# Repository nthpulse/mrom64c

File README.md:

# mrom64c
char and kernal rom replacement for the c64 250469 board

part of the MROM64 project: https://nthpulse.net/projects/mrom64/

details & instruction for this circuit board:
https://nthpulse.net/projects/mrom64/boards/mrom64c/

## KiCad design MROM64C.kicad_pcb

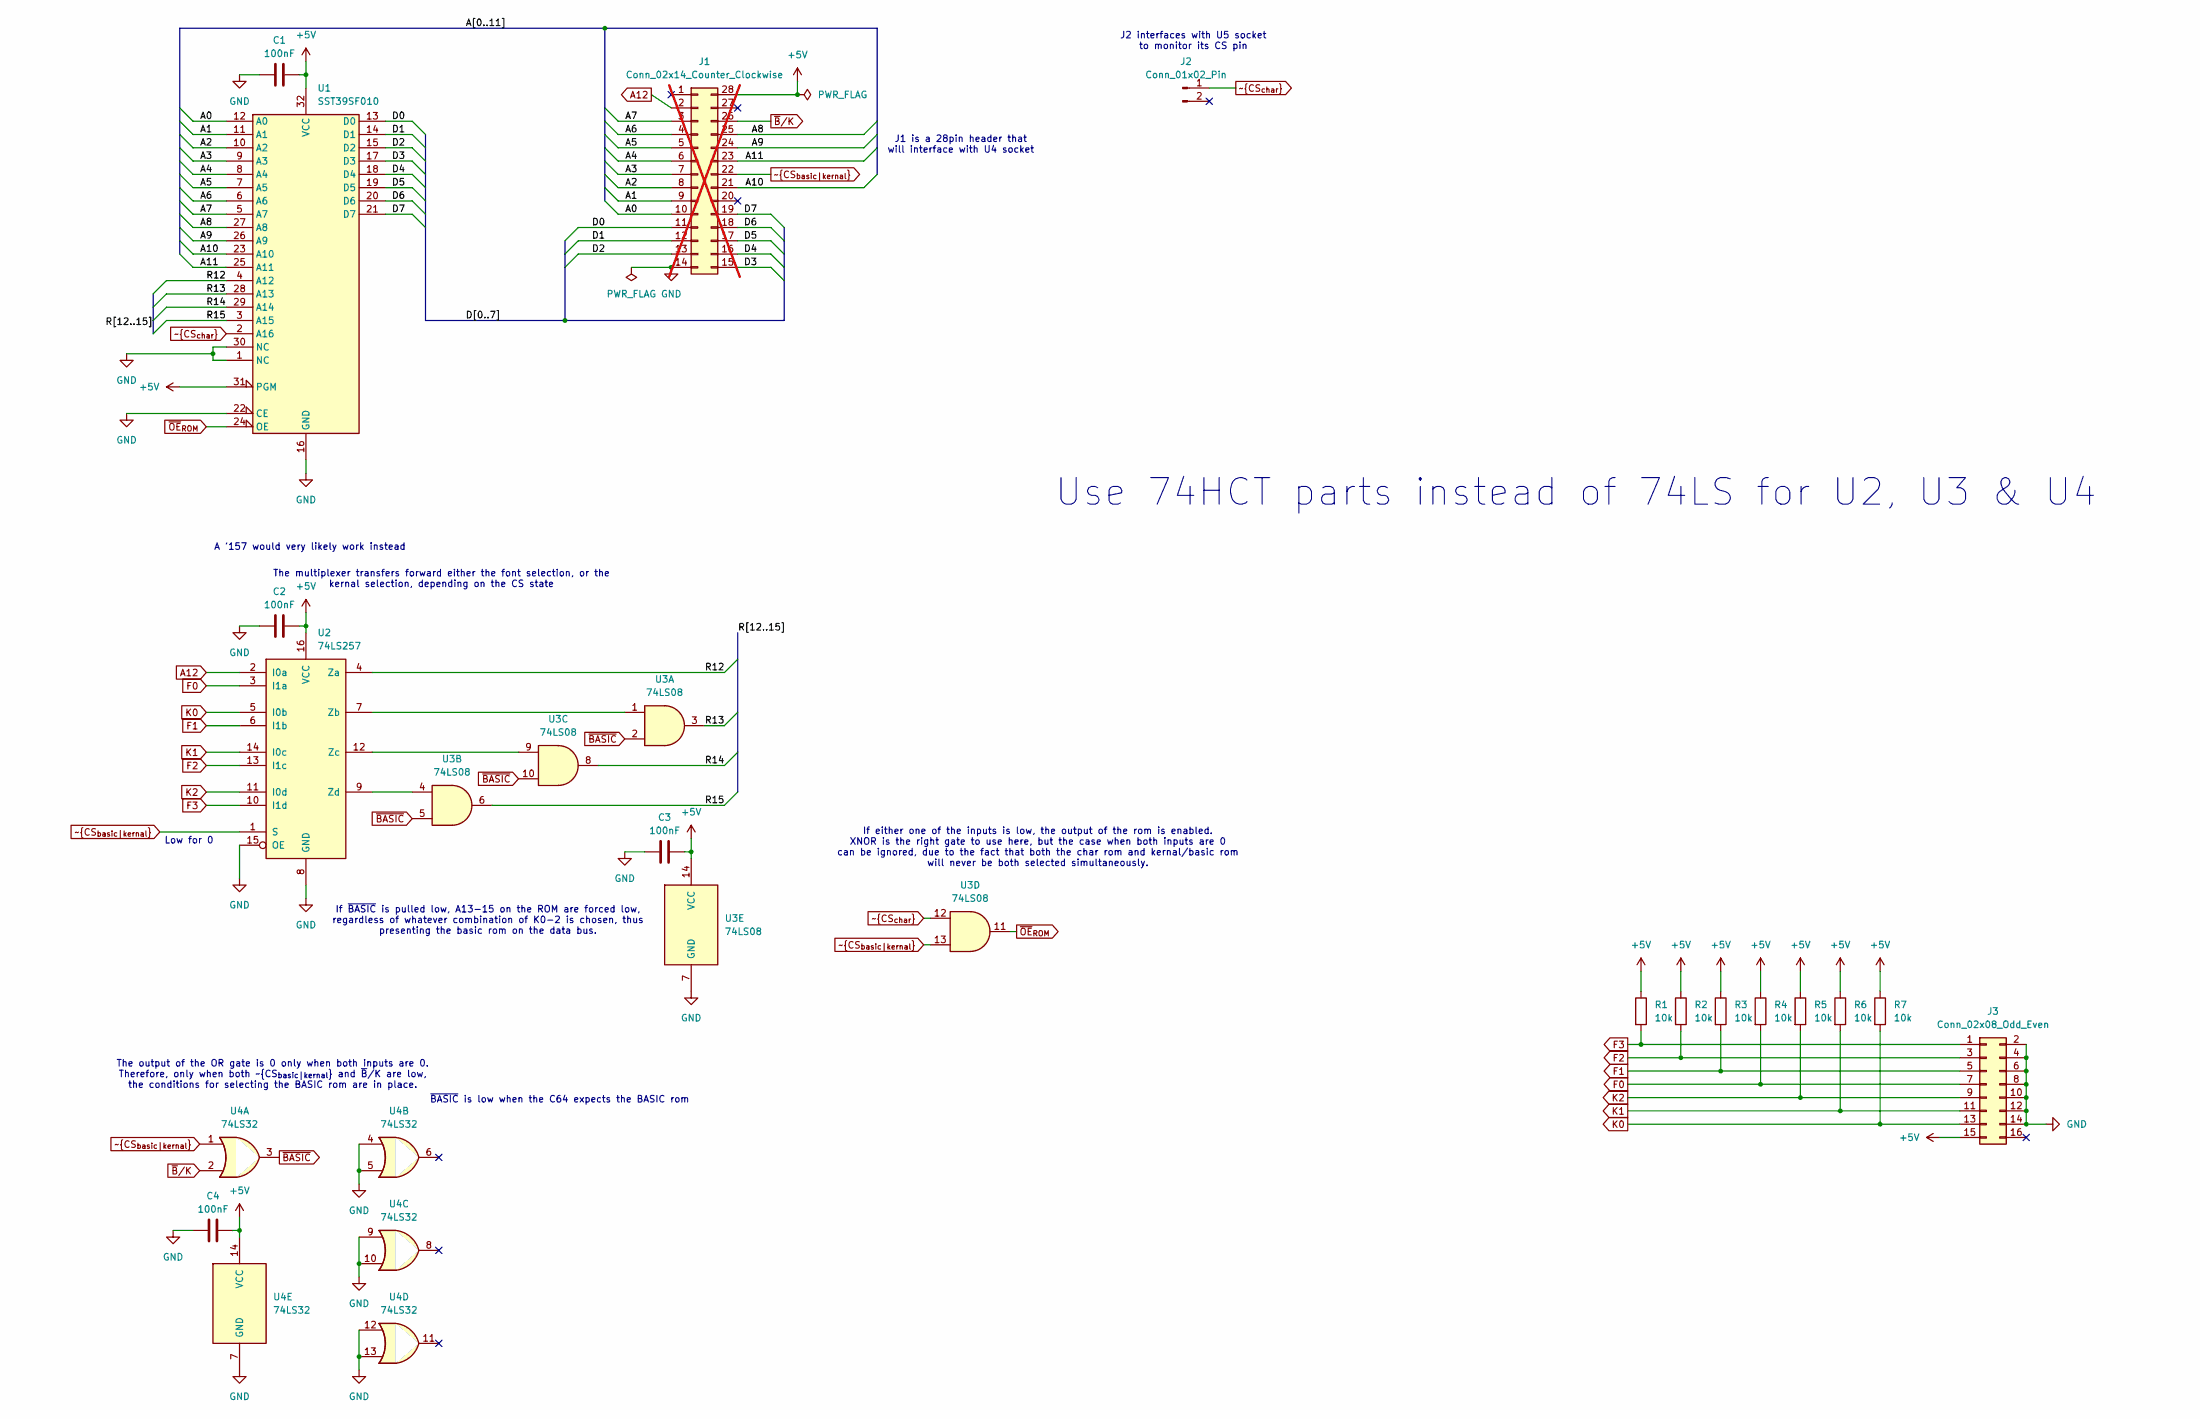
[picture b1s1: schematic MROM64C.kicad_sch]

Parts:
C1, C2, C3, C4: 100nF; C_0805_2012Metric_Pad1.18x1.45mm_HandSolder
J1: Conn_02x14_Counter_Clockwise; DIP-28_W15.24mm; not fitted
J2: Conn_01x02_Pin; PinHeader_1x02_P2.54mm_Vertical
J3: Conn_02x08_Odd_Even; PinHeader_2x08_P2.54mm_Vertical
R1, R2, R3, R4, R5, R6, R7: 10k; R_0805_2012Metric_Pad1.15x1.40mm_HandSolder
U1: SST39SF010; DIP-32_W15.24mm_Socket
U2: 74LS257; SOIC-16_3.9x9.9mm_P1.27mm
U3: 74LS08; SOIC-14_3.9x8.7mm_P1.27mm
U4: 74LS32; SOIC-14_3.9x8.7mm_P1.27mm

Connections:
+5V: C1.2, C2.2, C3.2, C4.2, J1.28, J3.15, R1.1, R2.1, R3.1, R4.1, R5.1, R6.1, R7.1, U1.31 (PGM), U1.32 (VCC), U2.16 (VCC), U3.14 (VCC), U4.14 (VCC)
/A0: J1.10, U1.12 (A0)
/A1: J1.9, U1.11 (A1)
/A2: J1.8, U1.10 (A2)
/A3: J1.7, U1.9 (A3)
/A4: J1.6, U1.8 (A4)
/A5: J1.5, U1.7 (A5)
/A6: J1.4, U1.6 (A6)
/A7: J1.3, U1.5 (A7)
/A8: J1.25, U1.27 (A8)
/A9: J1.24, U1.26 (A9)
/A10: J1.21, U1.23 (A10)
/A11: J1.23, U1.25 (A11)
/D0: J1.11, U1.13 (D0)
/D1: J1.12, U1.14 (D1)
/D2: J1.13, U1.15 (D2)
/D3: J1.15, U1.17 (D3)
/D4: J1.16, U1.18 (D4)
/D5: J1.17, U1.19 (D5)
/D6: J1.18, U1.20 (D6)
/D7: J1.19, U1.21 (D7)
/R12: U1.4 (A12), U2.4 (Za)
/R13: U1.28 (A13), U3.3
/R14: U1.29 (A14), U3.8
/R15: U1.3 (A15), U3.6
A12: J1.2, U2.2 (I0a)
F0: J3.7, R4.2, U2.3 (I1a)
F1: J3.5, R3.2, U2.6 (I1b)
F2: J3.3, R2.2, U2.13 (I1c)
F3: J3.1, R1.2, U2.10 (I1d)
GND: C1.1, C2.1, C3.1, C4.1, J1.14, J3.2, J3.4, J3.6, J3.8, J3.10, J3.12, J3.14, U1.1 (NC), U1.16 (GND), U1.22 (CE), U1.30 (NC), U2.8 (GND), U2.15 (OE), U3.7 (GND), U4.4, U4.5, U4.7 (GND), U4.9, U4.10, U4.12, U4.13
K0: J3.13, R7.2, U2.5 (I0b)
K1: J3.11, R6.2, U2.14 (I0c)
K2: J3.9, R5.2, U2.11 (I0d)
unnamed: U2.7 (Zb), U3.1
unnamed: U2.12 (Zc), U3.9
unnamed: U2.9 (Zd), U3.4
~BASIC: U3.2, U3.5, U3.10, U4.3
~B/K: J1.26, U4.2
~CS_{basic|kernal}: J1.22, U2.1 (S), U3.13, U4.1
~CS_{char}: J2.1, U1.2 (A16), U3.12
~OE_{ROM}: U1.24 (OE), U3.11

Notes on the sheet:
If either one of the inputs is low, the output of the rom is enabled. XNOR is the right gate to use here, but the case when both inputs are 0 can be ignored, due to the fact that both the char rom and kernal/basic rom will never be both selected simultaneously.
J2 interfaces with U5 socket to monitor its CS pin
The output of the OR gate is 0 only when both inputs are 0. Therefore, only when both ~{CS_{basic|kernal}} and ~{B}/K are low, the conditions for selecting the BASIC rom are in place.
~{BASIC} is low when the C64 expects the BASIC rom
If ~{BASIC} is pulled low, A13-15 on the ROM are forced low, regardless of whatever combination of K0-2 is chosen, thus presenting the basic rom on the data bus.
Use 74HCT parts instead of 74LS for U2, U3 & U4
A '157 would very likely work instead
Low for 0
J1 is a 28pin header that will interface with U4 socket
The multiplexer transfers forward either the font selection, or the kernal selection, depending on the CS state

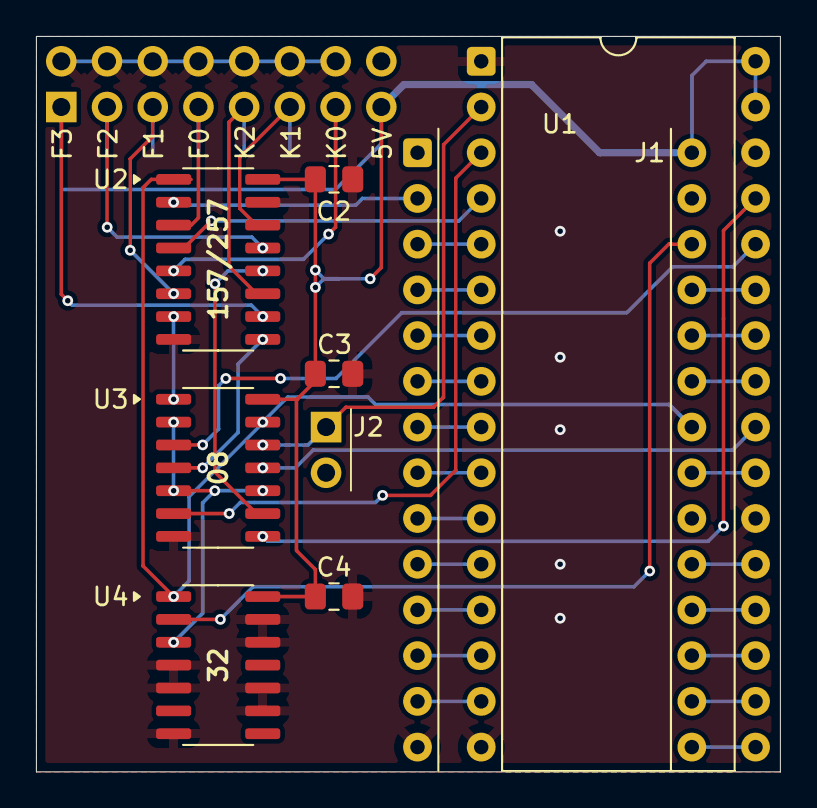
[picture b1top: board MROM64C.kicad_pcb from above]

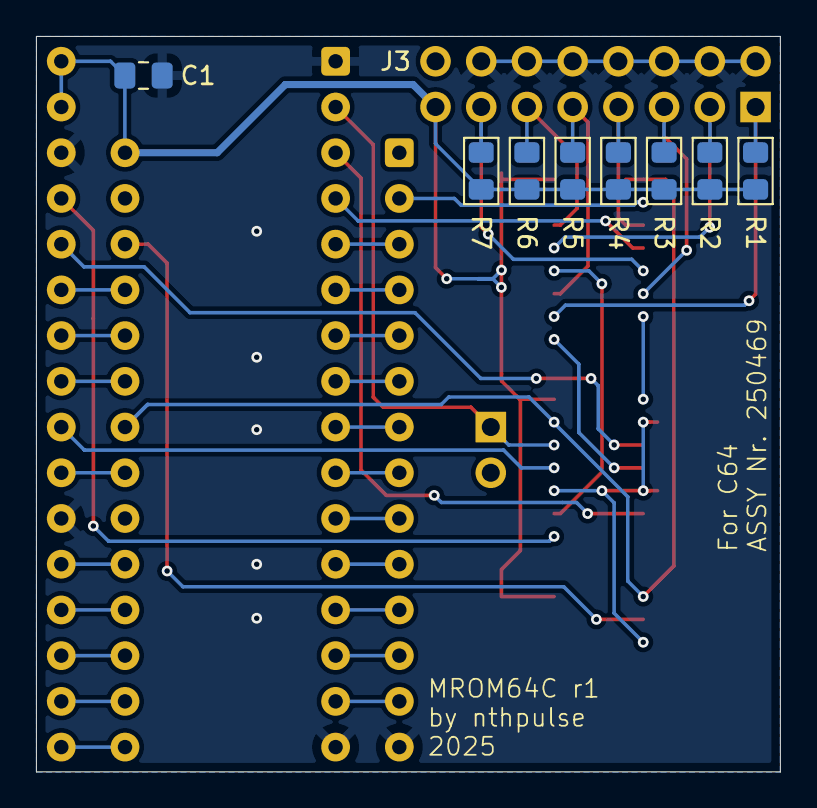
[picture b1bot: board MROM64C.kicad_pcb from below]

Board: 2 copper layers, 41.3 x 40.9 mm, 18 parts (9 on the bottom side), 42 nets.

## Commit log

2026-03-04 Uploaded project files
